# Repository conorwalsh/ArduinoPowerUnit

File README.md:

# Arduino Power Unit

Description
-----------

This project is a power unit for an Arduino Microcontroller.
The unit is supplied power using a 9V wall adapter and a 9V battery.
When AC power is available the unit draws power from the wall adapter, if there is a power cut the unit seamlessly switches to the battery as a power source and back when power is available.
During a power cut an LED is lit to alert the user that mains power is not available. There is also an LED to warn the user when the batteries are low.

Schematics
-----------

This is a very basic schamatic of how the device switches between mains and battery power using diodes. It will always use the side with the highest voltage and since the wall adapter will always have a higher voltage (≈9.3V) it will draw from that and not the battery (≤9V) but when the power goes out the adapter voltage falls to 0V and it draws from battery. There should be little to no leakage from the battery using this method.<br/>

This is a breadboard schematic of the final circuit.<br/>

This a photo of the breadboard circuit.<br/>

This is a standard schamatic of the final circuit.<br/>

This is the Printed Circuit Board Layout of the circuit.<br/>

This is a photo of the PCB without components.<br/>

This is a photo of the finished PCB with components.<br/>

License (MIT)
------
Copyright (c) 2016 Conor Walsh 

Permission is hereby granted, free of charge, to any person obtaining a copy
of this software and associated documentation files (the "Software"), to deal
in the Software without restriction, including without limitation the rights
to use, copy, modify, merge, publish, distribute, sublicense, and/or sell
copies of the Software, and to permit persons to whom the Software is
furnished to do so, subject to the following conditions:

The above copyright notice and this permission notice shall be included in all
copies or substantial portions of the Software.

THE SOFTWARE IS PROVIDED "AS IS", WITHOUT WARRANTY OF ANY KIND, EXPRESS OR
IMPLIED, INCLUDING BUT NOT LIMITED TO THE WARRANTIES OF MERCHANTABILITY,
FITNESS FOR A PARTICULAR PURPOSE AND NONINFRINGEMENT. IN NO EVENT SHALL THE
AUTHORS OR COPYRIGHT HOLDERS BE LIABLE FOR ANY CLAIM, DAMAGES OR OTHER
LIABILITY, WHETHER IN AN ACTION OF CONTRACT, TORT OR OTHERWISE, ARISING FROM,
OUT OF OR IN CONNECTION WITH THE SOFTWARE OR THE USE OR OTHER DEALINGS IN THE
SOFTWARE.

Thanks
------

Thank you for taking the time to look at this project I hope that it is of use to you,<br/>
<br/>
Conor Walsh.

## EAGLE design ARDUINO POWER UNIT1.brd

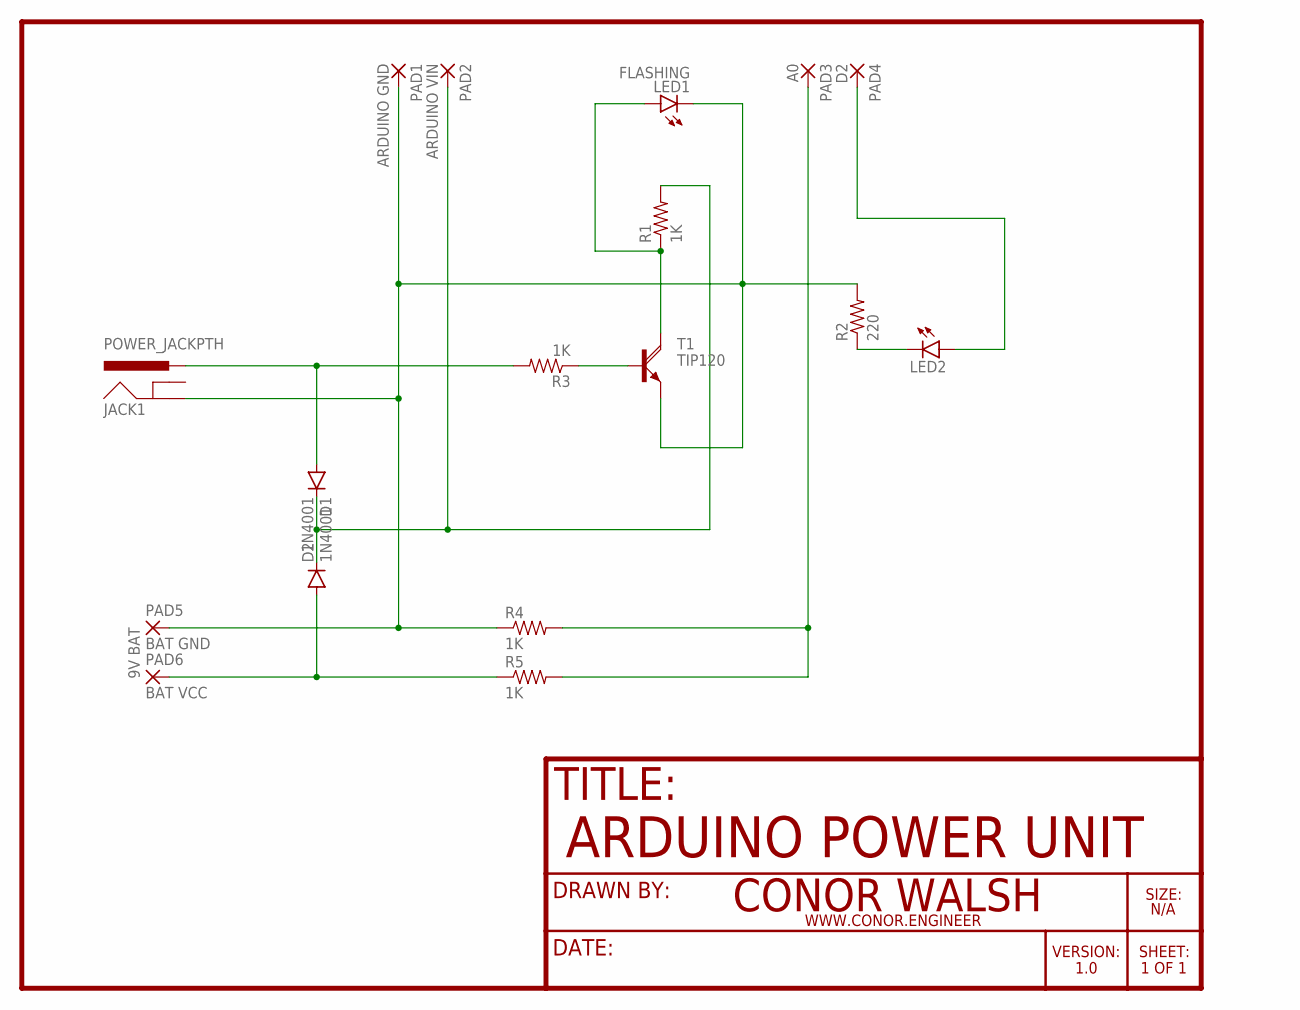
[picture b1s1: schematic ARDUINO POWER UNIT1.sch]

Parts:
D1, D2: 1N4001; DIODE-1N4148
JACK1: POWER_JACKPTH; POWER_JACK_PTH
LED1: FLASHING; LED5MM
LED2: LED5MM
PAD1: ARDUINO GND; 2,54/0,9
PAD2: ARDUINO VIN; 2,54/0,9
PAD3: A0; 2,54/0,9
PAD4: D2; 2,54/0,9
PAD5: BAT GND; 2,54/0,9
PAD6: BAT VCC; 2,54/0,9
R1, R3, R4, R5: 1K; AXIAL-0.4
R2: 220; AXIAL-0.4
T1: TIP120; TO220AH

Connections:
unnamed: D1.A, JACK1.PWR, R3.P$2 (2)
unnamed: PAD3.1, R4.P$2 (2), R5.P$2 (2)
unnamed: R3.P$1 (1), T1.B
unnamed: LED1.A, R1.P$1 (1), T1.C
unnamed: D2.A, PAD6.1, R5.P$1 (1)
unnamed: JACK1.GND, LED1.K (C), PAD1.1, PAD5.1, R2.P$2 (2), R4.P$1 (1), T1.E
unnamed: LED2.K (C), R2.P$1 (1)
unnamed: LED2.A, PAD4.1
unnamed: D1.C, D2.C, PAD2.1, R1.P$2 (2)

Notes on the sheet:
TITLE:
DRAWN BY:
DATE:
SHEET:
SIZE:
N/A
1 OF 1
VERSION:
ARDUINO POWER UNIT
CONOR WALSH
WWW.CONOR.ENGINEER
1.0
9V BAT

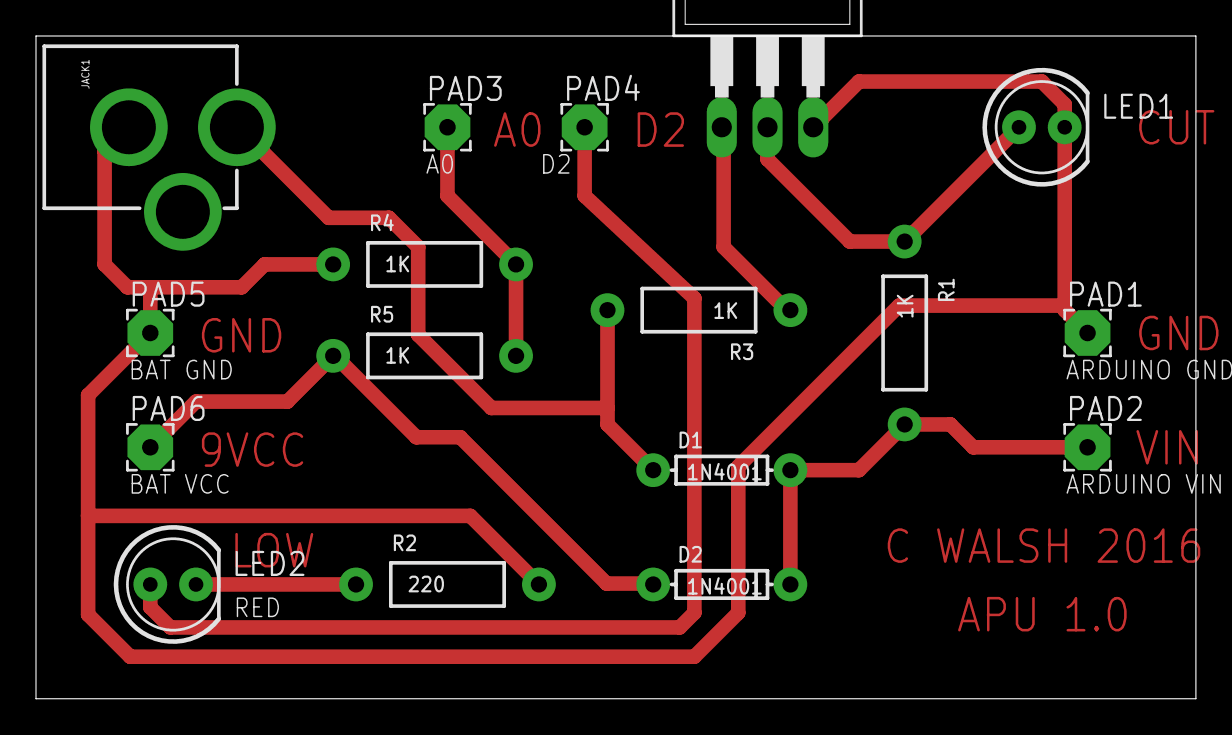
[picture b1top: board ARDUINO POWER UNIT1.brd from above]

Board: 2 copper layers, 64.4 x 36.8 mm, 17 parts (0 on the bottom side), 9 nets.

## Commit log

2016-07-24 Fixed incorrect inequality
2016-07-24 Fixed incorrect image URL

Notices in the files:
parts and their libraries:
SparkFun-DiscreteSemi: Licensing: Creative Commons ShareAlike 4.0 International - https://creativecommons.org/licenses/by-sa/4.0
